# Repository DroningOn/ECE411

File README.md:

ECE411 Practicum Project
========================

**Project Focus:** Classroom Interactive Device

**Team:** Chris Halseth, Kyle Lu, Matt Downey, Michael Schmidt

**Advisor:** Andrew Greenberg

**Schematics and Layout**
(right click, save link as)

* [Satellite Board Schematic] (https://raw.githubusercontent.com/DroningOn/ECE411/master/Eagle/Schematics%20&%20Board%20Layout/Tx%20Board%20Schematic/T08-TxClicker-Rev1a.sch)

* [Satellite Board Layout] (https://raw.githubusercontent.com/DroningOn/ECE411/master/Eagle/Schematics%20&%20Board%20Layout/Tx%20Board%20Schematic/T08-TxClicker-Rev1a.brd)

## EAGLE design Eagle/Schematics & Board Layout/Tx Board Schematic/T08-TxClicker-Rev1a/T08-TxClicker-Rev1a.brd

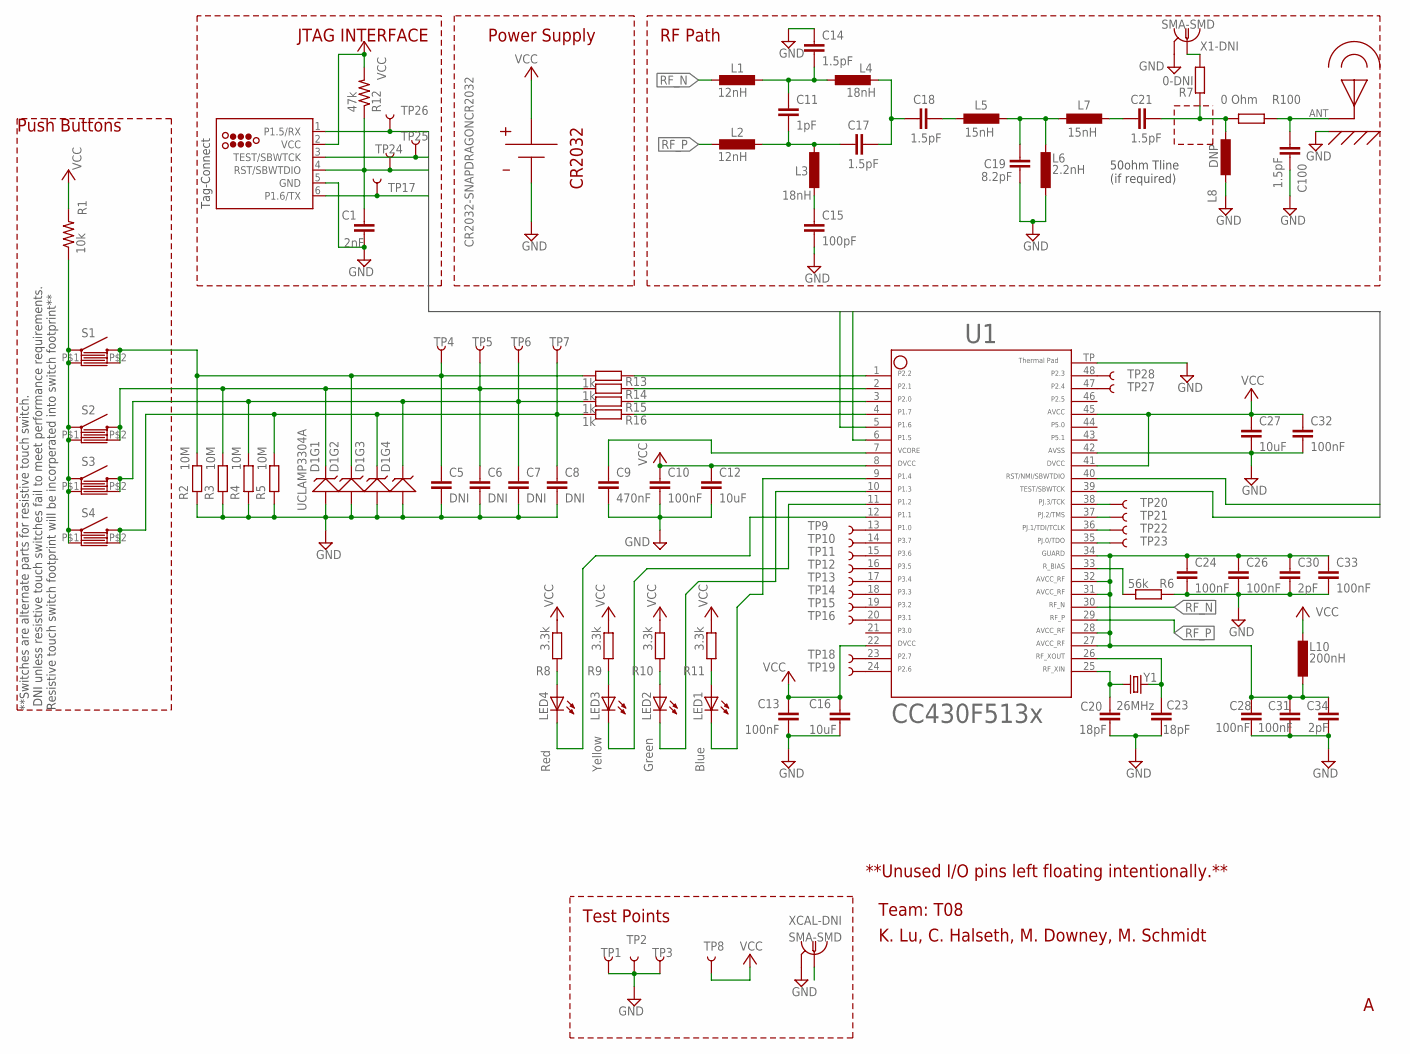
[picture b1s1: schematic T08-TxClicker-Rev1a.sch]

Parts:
C1: 2nF; C0603
C5, C6, C7, C8: DNI; C0603
C9: 470nF; C0603
C10, C13, C24, C26, C28, C31, C32, C33: 100nF; C0603
C11: 1pF; C0402
C12, C16, C27: 10uF; C0603
C14, C17, C18, C21, C100: 1.5pF; C0402
C15: 100pF; C0402
C19: 8.2pF; C0402
C20, C23: 18pF; C0603
C30, C34: 2pF; C0603
D1: UCLAMP3304A; SOT666
L1, L2: 12nH; L0402
L3, L4: 18nH; L0402
L5, L7: 15nH; L0402
L6: 2.2nH; L0402
L8: DNP; L0402
L10: 200nH; L0603
LED1: Blue; CHIP-LED0603
LED2: Green; CHIP-LED0603
LED3: Yellow; CHIP-LED0603
LED4: Red; CHIP-LED0603
R1: 10k; R0603
R2, R3, R4, R5: 10M; R0603
R6: 56k; R0603
R7: 0-DNI; R0603
R8, R9, R10, R11: 3.3k; R0603
R12: 47k; R0603
R13, R14, R15, R16: 1k; R0603
R100: 0 Ohm; R0402
S1, S2, S3, S4: TOUCHPAD_SWITCH_COMBOSWITC_TOUCHPAD; TACTILE-PTH-12MM
TP1, TP2, TP3, TP4, TP5, TP6, TP7, TP8, TP10, TP11, TP12, TP13, TP14, TP15, TP16, TP17, TP18, TP19, TP20, TP21, TP22, TP23, TP24, TP25, TP26, TP27, TP28: TEST-POINT3; PAD.03X.03
TP9: TP9; PAD.03X.03
U1: CC430F513X---RGZ48; RGZ48
U$1: TC2030-MCP
U$5: CR2032-SNAPDRAGONCR2032; CR2032-SNAPDRAGON
U$6: PCB_ANTENNA_915MHZOSHP; PCB_ANTENNA_915MHZ
X1-DNI: SMA-SMD
XCAL-DNI: SMA-SMD
Y1: 26MHz; CRYSTAL-TXC-7A

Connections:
ANTENNA: C100.P$2 (2), R100.P$1 (1), U$6.ANT
GND: C1.2, C5.2, C6.2, C7.2, C8.2, C9.2, C10.2, C12.2, C13.2, C14.P$1 (1), C15.P$2 (2), C16.2, C19.P$1 (1), C20.2, C23.2, C24.2, C26.2, C27.2, C28.2, C30.2, C31.2, C32.2, C33.2, C34.2, C100.P$1 (1), D1.2, D1.5 (2), L6.P$2 (2), L8.P$1 (1), R2.1, R3.1, R4.1, R5.1, R6.1, TP1.P$1, TP2.P$1, TP3.P$1, U1.42, U1.TP (49), U$1.5 (GND), U$5.V-, U$6.GPLANE (GND), X1-DNI.2@1 (2), X1-DNI.2@2 (2), X1-DNI.2@3 (2), X1-DNI.2@4 (2), X1-DNI.2@5 (2), X1-DNI.2@6 (2), XCAL-DNI.2@1 (2), XCAL-DNI.2@2 (2), XCAL-DNI.2@3 (2), XCAL-DNI.2@4 (2), XCAL-DNI.2@5 (2), XCAL-DNI.2@6 (2)
unnamed: C11.P$2 (2), C17.P$2 (2), L2.P$1 (1), L3.P$1 (1)
unnamed: C11.P$1 (1), C14.P$2 (2), L1.P$1 (1), L4.P$2 (2)
unnamed: C17.P$1 (1), C18.P$1 (1), L4.P$1 (1)
unnamed: C15.P$1 (1), L3.P$2 (2)
unnamed: C18.P$2 (2), L5.P$1 (1)
unnamed: C19.P$2 (2), L5.P$2 (2), L6.P$1 (1), L7.P$1 (1)
unnamed: R16.2, U1.4
unnamed: C21.P$2 (2), L7.P$2 (2)
unnamed: R15.2, U1.3
unnamed: LED2.C, U1.10
unnamed: R1.1, S1.1 (BASE), S1.P$1 (BASE), S2.1 (BASE), S2.P$1 (BASE), S3.1 (BASE), S3.P$1 (BASE), S4.1 (BASE), S4.P$1 (BASE)
unnamed: C21.P$1 (1), L8.P$2 (2), R7.1, R100.P$2 (2)
unnamed: LED4.A, R8.1
unnamed: LED3.A, R9.1
unnamed: LED3.C, U1.11
unnamed: LED2.A, R10.1
unnamed: LED1.A, R11.1
unnamed: LED4.C, U1.12
unnamed: R14.2, U1.2
unnamed: R13.2, U1.1
unnamed: TP13.P$1, U1.17
unnamed: TP9.P$1, U1.13
unnamed: TP10.P$1, U1.14
unnamed: TP11.P$1, U1.15
unnamed: TP12.P$1, U1.16
unnamed: TP14.P$1, U1.18
unnamed: TP15.P$1, U1.19
unnamed: TP16.P$1, U1.20
unnamed: TP18.P$1, U1.23
unnamed: TP19.P$1, U1.24
unnamed: TP27.P$1, U1.47
unnamed: TP28.P$1, U1.48
P1.4: LED1.C, U1.9
P1.5/RX: TP26.P$1, U1.6, U$1.1 (P1.5/RX)
P1.6/TX: TP17.P$1, U1.5, U$1.6 (P1.6/TX)
P1.7: C8.1, D1.4, R5.2, R16.1, S4.3 (TOP), S4.P$2 (TOP), TP7.P$1
P2.0: C7.1, D1.6, R4.2, R15.1, S3.3 (TOP), S3.P$2 (TOP), TP6.P$1
P2.1: C6.1, D1.1, R3.2, R14.1, S2.3 (TOP), S2.P$2 (TOP), TP5.P$1
P2.2: C5.1, D1.3 (1), R2.2, R13.1, S1.3 (TOP), S1.P$2 (TOP), TP4.P$1
PJ.0/TDO: TP23.P$1, U1.35
PJ.1/TDI/TCLK: TP22.P$1, U1.36
PJ.2/TMS: TP21.P$1, U1.37
PJ.3/TCK: TP20.P$1, U1.38
RF_N: L1.P$2 (2), U1.30
RF_P: L2.P$2 (2), U1.29
RF_PWR: C24.1, C26.1, C28.1, C30.1, C31.1, C33.1, C34.1, L10.2, U1.27, U1.28, U1.31, U1.32, U1.34
RF_TEST_50OHM: R7.2, X1-DNI.1
RF_XIN: C20.1, U1.25, Y1.P$1 (1)
RF_XOUT: C23.1, U1.26, Y1.P$2 (2)
RST/NMI/SBWTDIO: C1.1, R12.1, TP24.P$1, U1.40, U$1.4 (RST/SBWTDIO)
R_BIAS: R6.2, U1.33
TEST50: XCAL-DNI.1
TEST/SBWTCK: TP25.P$1, U1.39, U$1.3 (TEST/SBWTCK)
VCC: C10.1, C12.1, C13.1, C16.1, C27.1, C32.1, L10.1, R1.2, R8.2, R9.2, R10.2, R11.2, R12.2, TP8.P$1, U1.8, U1.22, U1.41, U1.45, U$1.2 (VCC), U$5.V+
VCORE: C9.1, U1.7

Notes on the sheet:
CR2032
RF Path
JTAG INTERFACE
K. Lu, C. Halseth, M. Downey, M. Schmidt
Team: T08
Push Buttons
**Unused I/O pins left floating intentionally.**
Test Points
50ohm Tline (if required)
Power Supply
Tag-Connect
**Switches are alternate parts for resistive touch switch. DNI unless resistive touch switches fail to meet performance requirements. Resistive touch switch footprint will be incorperated into switch footprint**

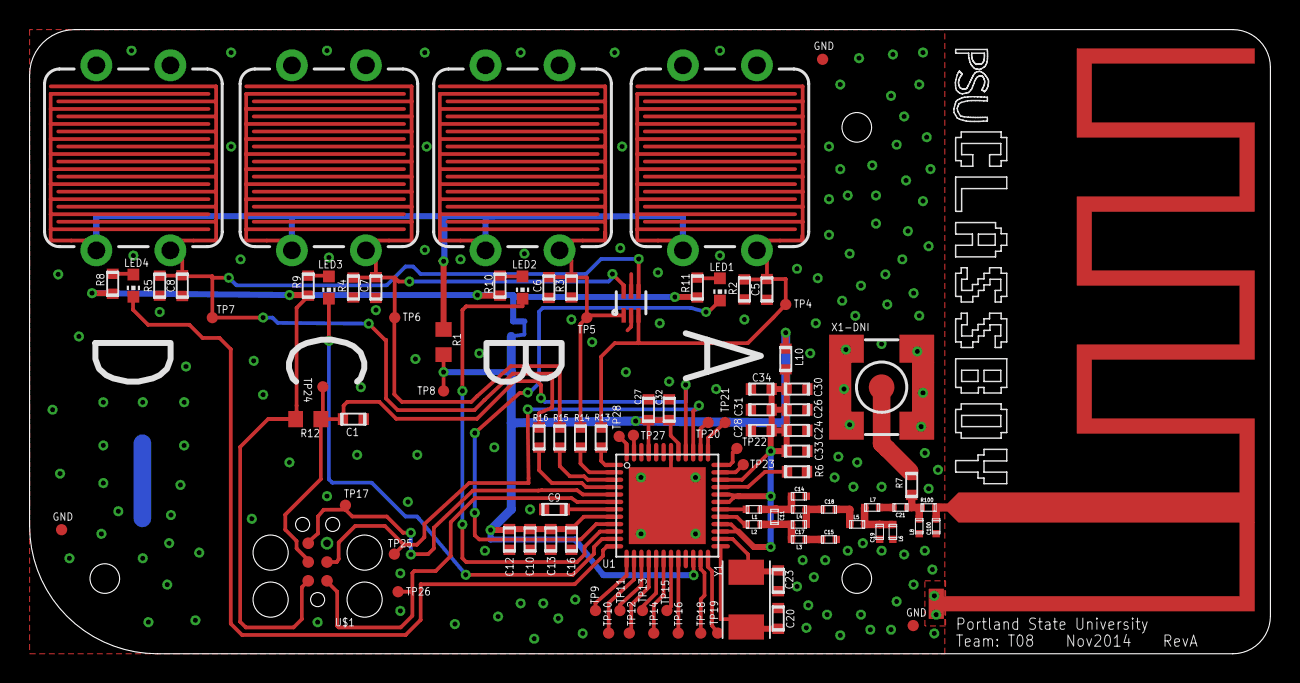
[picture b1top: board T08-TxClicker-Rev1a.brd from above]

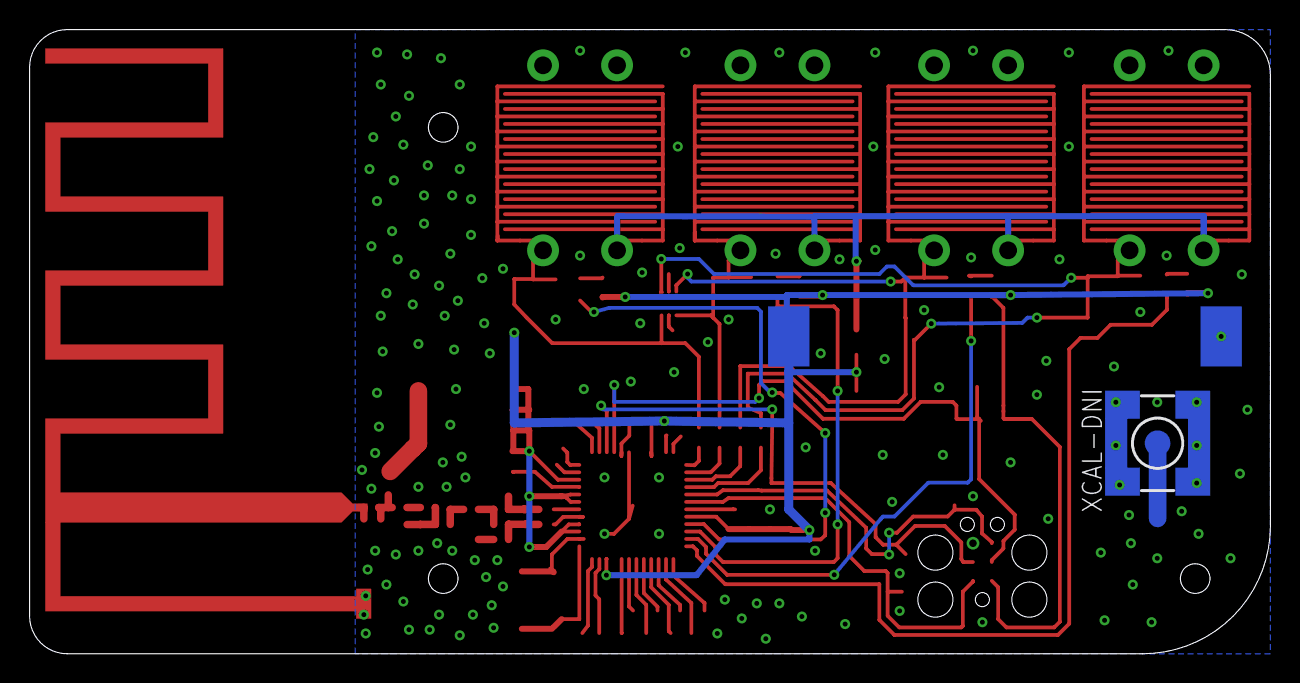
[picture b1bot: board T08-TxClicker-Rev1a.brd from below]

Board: 2 copper layers, 83.8 x 42.2 mm, 99 parts (2 on the bottom side), 56 nets.

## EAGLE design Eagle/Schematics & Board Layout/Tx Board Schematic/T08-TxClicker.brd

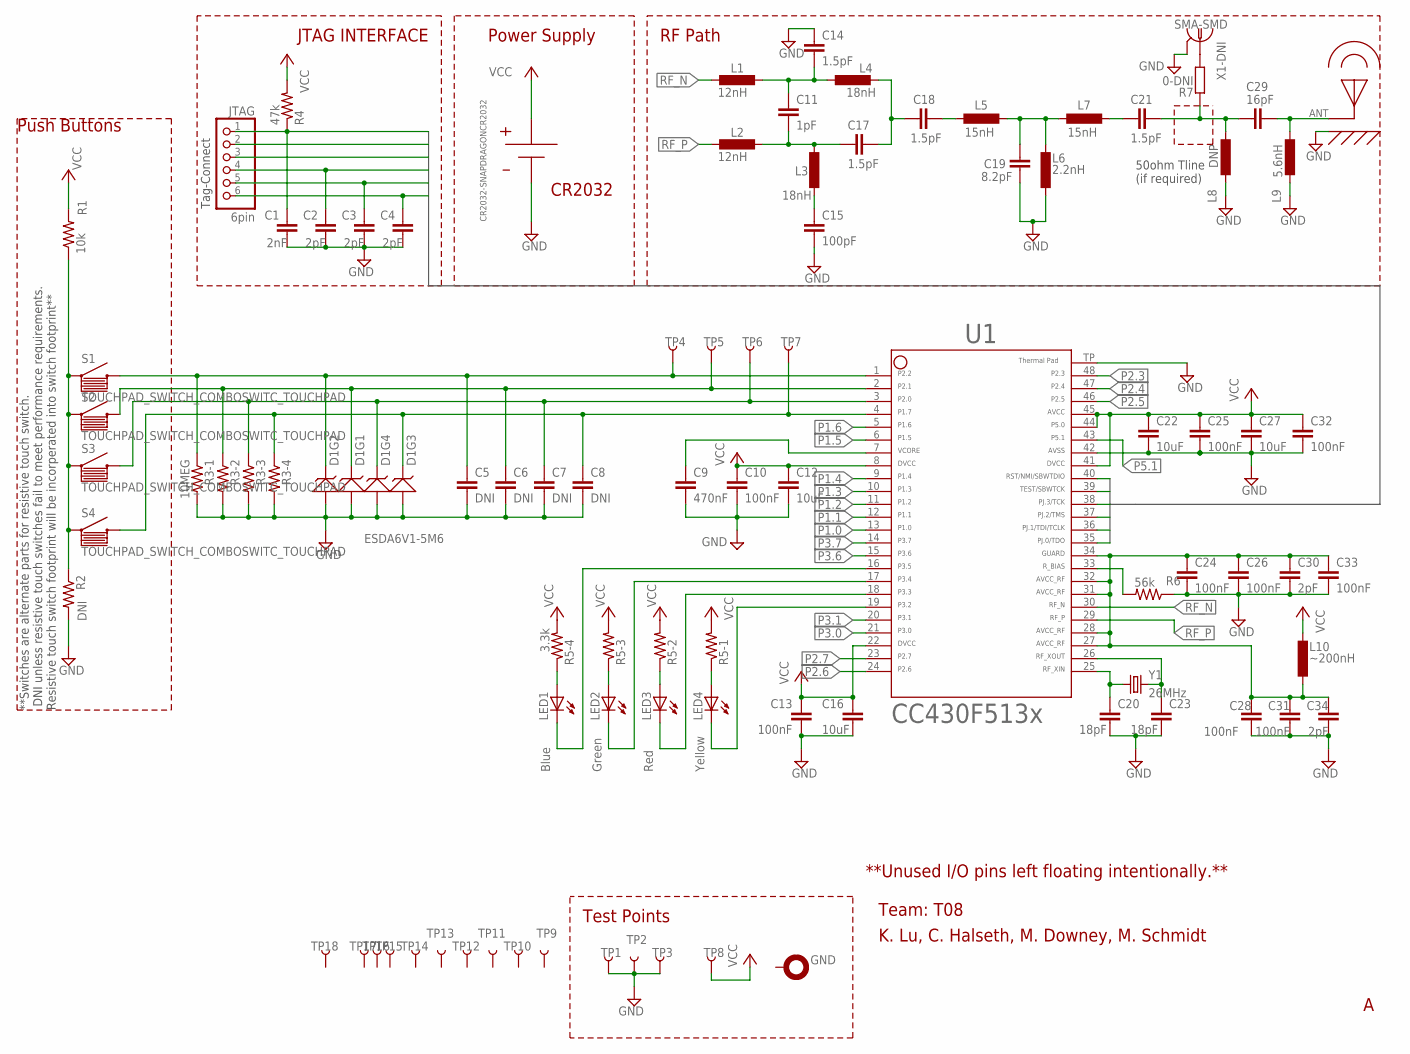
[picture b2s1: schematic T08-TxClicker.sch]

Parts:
C1: 2nF; C0603
C2, C3, C4, C30, C34: 2pF; C0603
C5, C6, C7, C8: DNI; C0603
C9: 470nF; C0603
C10, C13, C24, C25, C26, C28, C31, C32, C33: 100nF; C0603
C11: 1pF; C0402
C12, C16, C22, C27: 10uF; C0805
C14, C17, C18, C21: 1.5pF; C0402
C15: 100pF; C0402
C19: 8.2pF; C0402
C20, C23: 18pF; C0402
C29: 16pF; C0402
D1: ESDA6V1-5M6; 5X-TVS
GND: STARBOARD_GND-SMALL2; STARBOARD_GROUND_SMALL2
JTAG: 6pin; 1X06
L1, L2: 12nH; L0402
L3, L4: 18nH; L0402
L5, L7: 15nH; L0402
L6: 2.2nH; L0402
L8: DNP; L0402
L9: 5.6nH; L0402
L10: ~200nH; L0603
LED1: Blue; CHIP-LED0603
LED2: Green; CHIP-LED0603
LED3: Red; CHIP-LED0603
LED4: Yellow; CHIP-LED0603
R1: 10k; R0603
R2: DNI; R0603
R3: 10MEG; 2012(4_RES)
R4: 47k; R0603
R5: 3.3k; 2012(4_RES)
R6: 56k; R0603
R7: 0-DNI; R0603
S1, S2, S3, S4: TOUCHPAD_SWITCH_COMBOSWITC_TOUCHPAD; TACTILE-PTH-12MM
TP1, TP2, TP3, TP4, TP5, TP6, TP7, TP8, TP9, TP10, TP11, TP12, TP13, TP14, TP15, TP16, TP17, TP18: TEST-POINT3; PAD.03X.03
U1: CC430F513X---RGZ48; RGZ48
U$5: CR2032-SNAPDRAGONCR2032; CR2032-SNAPDRAGON
U$6: PCB_ANTENNA_915MHZOSHP; PCB_ANTENNA_915MHZ
X1-DNI: SMA-SMD
Y1: 26MHz; CRYSTAL-TXC-7A

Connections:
ANTENNA: C29.P$1 (1), L9.P$2 (2), U$6.ANT
GND: C1.2, C2.2, C3.2, C4.2, C5.2, C6.2, C7.2, C8.2, C9.2, C10.2, C12.2, C13.2, C14.P$1 (1), C15.P$2 (2), C16.2, C19.P$1 (1), C20.2, C22.2, C23.2, C24.2, C25.2, C26.2, C27.2, C28.2, C30.2, C31.2, C32.2, C33.2, C34.2, D1.2, L6.P$2 (2), L8.P$1 (1), L9.P$1 (1), R2.2, R3.2, R3.4 (2), R3.6 (2), R3.8 (2), R6.1, TP1.P$1, TP2.P$1, TP3.P$1, U1.42, U1.TP (49), U$5.V-, U$6.GPLANE, X1-DNI.2@1 (2), X1-DNI.2@2 (2), X1-DNI.2@3 (2), X1-DNI.2@4 (2), X1-DNI.2@5 (2), X1-DNI.2@6 (2)
unnamed: C11.P$2 (2), C17.P$2 (2), L2.P$1 (1), L3.P$1 (1)
unnamed: C11.P$1 (1), C14.P$2 (2), L1.P$1 (1), L4.P$2 (2)
unnamed: C17.P$1 (1), C18.P$1 (1), L4.P$1 (1)
unnamed: C15.P$1 (1), L3.P$2 (2)
unnamed: C18.P$2 (2), L5.P$1 (1)
unnamed: C19.P$2 (2), L5.P$2 (2), L6.P$1 (1), L7.P$1 (1)
unnamed: C21.P$2 (2), L7.P$2 (2)
unnamed: C24.1, C26.1, C28.1, C30.1, C31.1, C33.1, C34.1, L10.2, U1.27, U1.28, U1.31, U1.32, U1.34
unnamed: R7.2, X1-DNI.1
unnamed: R1.1, R2.1, S1.1, S2.1, S3.1, S4.1
unnamed: C21.P$1 (1), C29.P$2 (2), L8.P$2 (2), R7.1
unnamed: LED1.A, R5.7 (1)
unnamed: LED2.A, R5.5 (1)
unnamed: LED3.A, R5.3 (1)
unnamed: LED4.A, R5.1
P1.0: U1.13
P1.1: U1.12
P1.2: U1.11
P1.3: U1.10
P1.4: U1.9
P1.5: U1.6
P1.6: U1.5
P1.7: C8.1, D1.4, R3.7 (1), S4.3 (2), TP7.P$1, U1.4
P2.0: C7.1, D1.5, R3.5 (1), S3.3 (2), TP6.P$1, U1.3
P2.1: C6.1, D1.1, R3.3 (1), S2.3 (2), TP5.P$1, U1.2
P2.2: C5.1, D1.3, R3.1, S1.3 (2), TP4.P$1, U1.1
P2.3: U1.48
P2.4: U1.47
P2.5: U1.46
P2.6: U1.24
P2.7: U1.23
P3.0: U1.21
P3.1: U1.20
P3.2: LED4.C, U1.19
P3.3: LED3.C, U1.18
P3.4: LED2.C, U1.17
P3.5: LED1.C, U1.16
P3.6: U1.15
P3.7: U1.14
P5.1: U1.43
PJ.0/TDO: C4.1, JTAG.6, U1.35
PJ.1/TDI/TCLK: C3.1, JTAG.5, U1.36
PJ.2/TMS: C2.1, JTAG.4, U1.37
PJ.3/TCK: JTAG.3, U1.38
RF_N: L1.P$2 (2), U1.30
RF_P: L2.P$2 (2), U1.29
RF_XIN: C20.1, U1.25, Y1.P$1 (1)
RF_XOUT: C23.1, U1.26, Y1.P$2 (2)
RST/NMI/SBWTDIO: C1.1, JTAG.1, R4.1, U1.40
R_BIAS: R6.2, U1.33
TEST/SBWTCK: JTAG.2, U1.39
VCC: C10.1, C12.1, C13.1, C16.1, C22.1, C25.1, C27.1, C32.1, L10.1, R1.2, R4.2, R5.2, R5.4 (2), R5.6 (2), R5.8 (2), TP8.P$1, U1.8, U1.22, U1.41, U1.44, U1.45, U$5.V+
VCORE: C9.1, U1.7

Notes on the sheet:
CR2032
RF Path
JTAG INTERFACE
K. Lu, C. Halseth, M. Downey, M. Schmidt
Team: T08
Push Buttons
**Unused I/O pins left floating intentionally.**
Test Points
50ohm Tline (if required)
Power Supply
Tag-Connect
**Switches are alternate parts for resistive touch switch. DNI unless resistive touch switches fail to meet performance requirements. Resistive touch switch footprint will be incorperated into switch footprint**

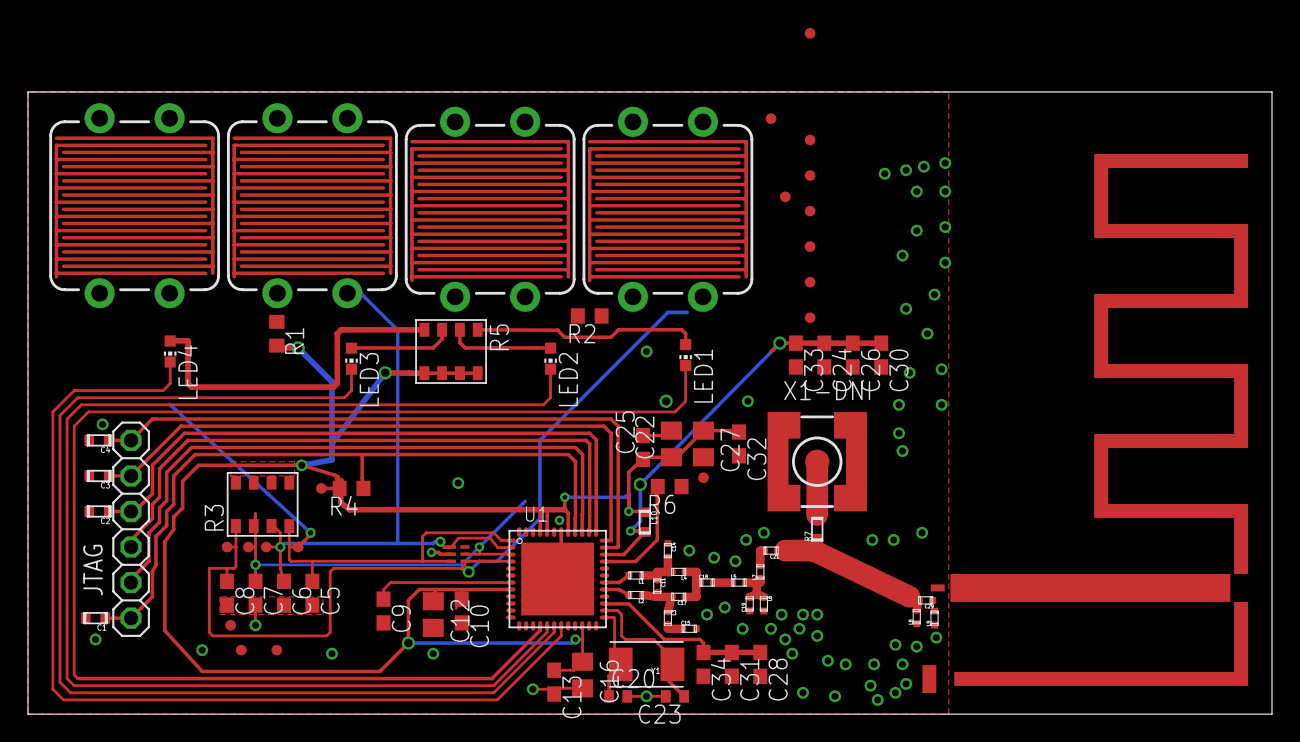
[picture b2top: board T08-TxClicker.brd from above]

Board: 2 copper layers, 88.9 x 44.5 mm, 84 parts (1 on the bottom side), 38 nets.

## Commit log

2014-10-11 Commit test
2014-10-11 Update test
2014-10-11 MCU Info
2014-10-13 ATMEL & Silicon Labs Datasheets
2014-10-13 Create adg-requirements.mdwn
    Ack! Forgot to push this last night, sorry.
2014-10-13 Rename adg-requirements.mdwn to adg-requirements.markdown
2014-10-13 README Update
2014-10-13 Fix..
2014-10-13 ECE 411 HW2
2014-10-15 Create Digikey-Parts-List
    Digikey Development PArts
2014-10-15 Wiki Materials
2014-10-15 CP2130 SPI-USB Bridge
    These datasheets describe the Silicon Labs CP2130 SPI to USB bridge IC
    and programming interface.
2014-10-16 Creating Active Datasheet Repo
    Put datasheets that we have confirmed in "Active Datasheets"
2014-10-16 Created Schematic with Part and Footprint
    Board Schematic has an Eagle project with the CC430F513x placed already.
    I included a separate folder with the library holding the footprints for
    the MSP430 series that might need to be installed on your end.
2014-10-16 Rename for clarity.
2014-10-16 Dev Kit User Guide
    Added user guide, renamed datasheet for part we are using CC430F5137 to
    clarify
2014-10-16 Schematic update
    Set up skeleton for match network on RF path. Inductor footprint
    probably needs to be changed.
2014-10-16 Ripped component libs out of dev kit schematics
    Wanted rlc_amber for SMD inductor footprints that eagle seemed to
    neglect.. like 0603. Pin headers might be useful later as well.
2014-10-16 Inductors updated with rlc_amber components
2014-10-16 PCB Antenna Stuff
    Baluns and filter network layed out, need to incorperate matching
    network (probably pi) and get a footprint kicked out for monopole
    antenna. NEED specs on substrate to do this correctly.
2014-10-17 Schematics & Board Layout Checklist
    See issue "PCB Checklist"
2014-10-17 Addl' Eagle Libraries and Datasheets
    The TI recommended CC430 to USB application note is really just for my
    own reference. They suggested using their own USB bridge requiring two
    chips; one chip is for the bridge, and another for eeprom parameter
    storage. That option isn't ideal, so we will use another option.
2014-10-17 FR-4 OSHPARK
2014-10-18 Project Files for Antenna Design
    Agilent ADS working files
2014-10-18 Antenna files update.
2014-10-18 Created HW Documents Folder in Wiki Materials
    Put assignments here and link to ECE411 Documents on Wiki
2014-10-18 Dropped space in name
2014-10-18 HomeworkPDF
2014-10-19 Eagle Libraries and Datasheets
    Created part for CR2032 surface mount battery holder.
    Added CC430 capacitive sensor application note.
2014-10-19 Schematic Update
    Added decoupling capacitors, JTAG interface, annotation.
2014-10-21 Revert "Schematic Update"
    This reverts commit 5abb39e3185d2877969b4b6a32f7c4948c4e0dd3.
2014-10-21 ADS Antenna Geometry with matching network solve
    Finished tuning simulations and creating match network for 915MHz,
    guessing no one else in the group has ADS so I will be migrating the
    specs into eagle this week.
2014-10-21 Pushed a plot out to show performance of match
2014-10-24 Antenna work and radio datasheets
2014-10-24 Tx-Schematic Added
    Additional eagle libraries; setup info added to datasheet section.
2014-10-24 Antenna Eagle Sym and Layout
2014-10-24 Layout updates
2014-10-24 Layout Work
2014-10-25 Materials BOM
    Created BOM, made pushbuttons larger on PCB
2014-10-25 Crystal stuff
2014-10-25 Quick board review.
2014-10-26 Paranoid Push of BOM (WIP)
2014-10-27 Tx-Schematic Update for Team Review
    Removed triple redundant capacitive sensor, removed MOSFET LED drivers,
    changed RF signal path to 0402 capacitors from 0603.
2014-10-27 Tx-Schematic update
2014-10-27 Tx-Schematic Update
    Changed pull-down to 10Meg, changed JTAG EMI cap from DNI to 2pF,
    Annotated JTAG as Tag-Connect
2014-10-27 TX_Schematic Update
2014-10-27 Eagle Library Update
2014-10-27 HW#3
2014-10-28 Directory cleanup
2014-10-28 WPR 2014-10-26 Compiled
2014-10-29 Antenna Field Stuff
    Needs to be updated again anyways because we know more about Gplane
    dimensions on the board now.
2014-10-29 Tidying up files
    Zipped old remote board and deleted source directory to avoid confusion.
    Created dated zip of active directory for sending files to others.
2014-10-29 Added GPIO TP
2014-10-29 Schematic update
2014-11-05 Touchpad switch layout lib updates
    TOUCHPAD_SWITCH_COMBO
2014-11-05 Eagle BRD Layout
    Incomplete, first pass layout
2014-11-05 Layout works
    o.O
2014-11-05 Eagle BRD Layout (rough)
    Squawk list:
    1) Antenna Pad
    2) Pushbutton pad
    3) VCC
    4) Capacitors not near pins
    5) Must optimize routing
2014-11-08 Project Schedule
    Rev 1
2014-11-08 Board relayout
    prelim, just a status update
2014-11-08 Board relayout
    Another check in.. tired going to bed.
2014-11-08 Ignore file for eagle temp files.
    Spam was annoying, poked around for this and found a repo with temp file
    cutters for major programs. Files will still exist locally but won't
    reach the repo
2014-11-08 Test
2014-11-08 test pt2
2014-11-08 Cleanup
    Missed some lol
2014-11-08 Schematic directory clean
2014-11-08 Layout Update
2014-11-08 50 Ohm Change
    Fat fingered dielectric constant in earlier calcs, fixed.
2014-11-08 LED reroute
2014-11-08 Tag connect part edit
    Based off mechanical drawings this should be a legit edit.. connector
    will be a bit wider on board but spacing should make it easier to sneak
    wires out.
2014-11-08 Missed some stuff.. not reading .gitignore for some reason
2014-11-08 test..
2014-11-08 Guess the file can't have a prename.
2014-11-08 Pushed connector holes back 25mil
2014-11-08 Button Example
2014-11-08 DRC free button
2014-11-09 Antenna redraw to reduce DRC
2014-11-09 Arranging silkscreen
2014-11-09 More Silkscreen
2014-11-09 Sparkfun master libs
    Yay footprints...
2014-11-09 And looking decent 0.o
2014-11-09 fill and crystal tweak
2014-11-09 Stop layer edit
2014-11-09 Move Tag Connect
    Vectorized fonts, moved tag connect, added tp labels
2014-11-09 Reset "switch"
2014-11-09 Added Measures and Layer Documentation
2014-11-09 Approved layer documentation errors
2014-11-09 moved some silkscreen
2014-11-09 Added M2 holes for board cover
    In case we decide to install a bamboo cover with nice engravings on top.
2014-11-09 Logo ftw?
2014-11-09 Merge remote-tracking branch 'origin/master'
    Conflicts:
    Eagle/Schematics & Board Layout/Tx Board
    Schematic/T08-TxClicker-Rev1a.brd
2014-11-09 Fixed all the component name overlaps with tStop
    Rest of tStop errors are from tPlace stuff, not fixing because I know
    how OSHPark treats that stuff
2014-11-09 Remove Empty layers, Added M2 holes
2014-11-09 Antenna geometry 0 width fix
    Pushed a DXF and freaked out cause antenna had no fill. Fixed by giving
    the poly a 1mil (I think or maybe 1um, doesn't matter) line width
2014-11-09 Lib to document push
2014-11-10 Revised Project Schedule
2014-11-10 Try this again
2014-11-10 Project Schedule rev 2
    Modified a couple dates
    Finished adding resources to tasks
    Finished load-leveling
2014-11-10 Project Schedule rev 3
    Changed to sort by resource
2014-11-10 Project Schedule rev 4
    Minor date tweaks
2014-11-10 wrong file
2014-11-10 Made PDF
2014-11-12 Updated silkscreen, added board preview
2014-11-13 Updated links to schematics and layout
2014-11-13 BOM Update
2014-11-17 Project Block Diagrams
    Gliffy is a Google Ghrome free add-on that can be used to view and edit
    the .gliffy files.
2014-11-17 Homework 5
2014-11-17 Update Homework#5 Figures
2014-11-19 T08HW6-Documentation
2014-11-19 Schematic Documentation for HW6
2014-11-20 Software Application rev 1
2014-11-20 Added Bar Graph Labels and make bars different colors
2014-11-21 Code migration and project integration
    Main working set in experimental, will be busting out sets to 5137/6137
    as they approach functionally finished.
2014-11-21 Making project portable.. probably a few more
2014-11-21 And more.
2014-11-21 ...CCS
2014-11-24 Rev 3
    -Changed a couple variables
    -Began Commenting
2014-11-24 Datasheet up
2014-11-24 Test Plan
2014-11-24 Further comments added
2014-11-25 rev 4
    -added menu bar
    -changed colors on bars
    -finished comments
2014-11-27 Working Rev
    -Polling duration drop down now sets polling duration
    -Added working Start Button and Stop Button
    -Bar graph now resets all bars to 0 upon new polling
    -Added countdown timer till end of polling
2014-11-27 Started spacing cleanup
2014-11-29 Working stuff yay.
    Need a bit of cleanup, just pushing archive of working project for now.
    Need to do cleanup still. Also, need to migrate my workspace onto git
    still.
2014-11-29 Workspace migration and some small bug fixes
    Should see updates as I made modifications now. Will need to have a sit
    down session to go over the general form of the source and do some
    cleanup.
2014-11-30 Unpushed laptop stuff for experimental
2014-12-02 Working Rev with serial
    CLASSBOY.py used for test without base station
    In Classboy with serial
    -added serial interface with base station
    -changed bar graphs to also show percentages
2014-12-06 Comments, comments everywhere
    -added a bunch of comments
2014-12-06 comment added
2014-12-07 settings export
2014-12-07 Comments and finishing touches
    -Finished commenting
    -Added ability to export to a csv file in excel format
2014-12-09 Finishing touches
2014-12-11 Final code additions
2014-12-11 Project cleanup
2014-12-11 More cleanup
    Probably going to be a bunch of these today, comments formatting etc.
    for project demo.
2014-12-11 Workspace sync
2014-12-11 Clean up, small bug fixes
2014-12-11 Local update of firmware on other device
2014-12-11 Inserted comment block on top
2014-12-11 Renamed software application
2014-12-11 Quick Fixes
2014-12-11 Added resizing based on most popular answer
2014-12-12 Changes, changes everywhere
    -changed bar graph resize to be off of total number of answers
    -implemented serial port checking for different base stations
2014-12-12 GitHub Maintenance
    File maintenance (moved all GERBER files in to folder, etc). BOM
    Presentable, GitHub file structure reasonable.
2014-12-12 More changes
2014-12-12 Trivial changes
    -added minimizing and restoring when polling and when polling is over,
    respectively
2014-12-12 Lengthened wait time
2014-12-12 ECE411 Presentation
2014-12-12 Final package and comments update
2014-12-12 lengthened sleep
2014-12-12 Committing Test Documentation for Matt
2014-12-13 Collection of Team WPR
2014-12-13 Reviewed my section of WPRs
    Found a missing week hiding in the email stream and inserted. (I had
    titled the email with the wrong week)
2014-12-13 Formatted Kyle and my WPR's to make easier to read
2014-12-14 finalizing stuff
2014-12-14 csv files from demo
2014-12-14 Added my WPRs
2014-12-14 Picture of completed Rev A device
2014-12-14 Merged the WPR's I had from Matt into team WPR
2014-12-14 Made image smaller lol.
2014-12-14 Put dates on Michael's WPR's

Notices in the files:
parts and their libraries:
SparkFun-FreqCtrl: Licensing: CC v3.0 Share-Alike You are welcome to use this library for commercial purposes.
SparkFun-Electromechanical--edited: Licensing: Creative Commons ShareAlike 4.0 International - https://creativecommons.org/licenses/by-sa/4.0
tagConnect: ©2009 ROFA.cz
